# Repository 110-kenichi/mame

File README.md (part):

MAmidiMEmo 6.4.2.1 Itoken (c)2019, 2025 / GPL-2.0

*** What is the MAmidiMEmo? ***

MAmidiMEmo is a virtual chiptune sound MIDI module using a MAME sound engine.
You can control various chips and make sound via MIDI I/F.
So, you don't need to use dedicated tracker and so on anymore. You can use your favorite MIDI sequencer to make a chip sound.

See samples
https://www.youtube.com/channel/UCGYO2bEPPIM2LTNDbBEDaAQ

MAmidiMEmo adopts multi timbre method. That mean you can play multi chords on MIDI 1ch if the chip has multi ch.

e.g.) YM2151 has 8ch FM sounds, so you can play 8 chords on MIDI 1ch or sharing 8ch with MIDI 16ch like a SC-55 and so on.
      As well, NES APU has 2ch for square wave, so you can play 2 chords on MIDI 1ch when select a square wave timbre.
	  However, when you select a triangle wave timbre, you can play 1 chord on MIDI 1ch. Because NES APU has only 1ch for triangle wave.

*** How to use MAmidiMEmo ***

0. Requirements

	*H/W

		CPU: Intel Core series CPU or equivalent, at least 2.0 GHz
		MEM: at least 4GB
		Sound: DirectSound capable sound card/onboard audio
		MIDI: MIDI IN I/F

	*S/W

		OS: Windows 10 or lator
		Runtime: .NET Framework 4.7 or lator
		         VC++ 2022 Runtime
					for 64bit: https://aka.ms/vs/17/release/vc_redist.x64.exe
					for 32bit: https://aka.ms/vs/17/release/vc_redist.x86.exe

1. Extract downloaded zip file.

   And execute "Set-ExecutionPolicy -Scope Process -ExecutionPolicy Bypass" on the PowerShell to allow script execution.
   Then execute "DelZoneID.ps1" on the PowerShell to remove "Zone.Identifier" flag.
   
   ★日本語フォルダには現状対応していません★

2. Install VC++ runtime 2022 and .NET Framework 4.7 or lator.

3. Launch MAmidiMEmo.exe

   Note: You can change the value of audio latency, sampling rate and audio output interface by [Tool] menu.
         PortAudio is a low latency sound engine. See http://www.portaudio.com/
   Note: Allow ★firewall communication to MAmidiMEmo and your DAW.

4. Select MIDI I/F from toolbar. MAmidiMEmo will recevie MIDI message from the selected MIDI I/F.

   Note: You can use the loopMIDI (See http://www.tobias-erichsen.de/software/loopmidi.html) to send MIDI message from this PC to MAmidiMEmo.

5. Add your favorite chips from the [Instruments] menu on the toolbar.

   Note: Currently supported chips are the following.

        YM2151, YM2612, YM3812, YM2413, YM2610B, YMF262
		YM2601 ★★★ Place legitimate ym2608_adpcm_rom.bin file in the Mami dir ★★★
        SID, POKEY, GB APU, SN76496, NES APU, MSM5232(+TA7630), AY-3-8910
        NAMCO CUS30, SCC, HuC6280
        C140, SPC700
        MT-32 ★★★ Place legitimate MT32_CONTROL.ROM and MT32_PCM.ROM files in the Mami dir ★★★
		CM-32P This is an incomplete simulator, not an emulator.
		       You can mod and add your custom sounds by editing tbl and sound font files.
		       Please contact me if you can help me to create CM-32P and SN-U110 sound fonts.
		TMS5220, SP0256, SAM

   Note: You can add the chip up to 8 per same chip type and MAmidiMEmo eats more CPU power.

6. Select the chip from the left pane and configure the chip on the right pane.

   *[Timbres]
    You can edit sound character from this property. It's selected by "Program Change" MIDI message.
	Please refer the following articles or MAME sources to understand these timbre parameters.

	YM2151:
	 https://www16.atwiki.jp/mxdrv/pages/24.html

	YM2612:
	 https://www.plutiedev.com/ym2612-registers
	 http://www.smspower.org/maxim/Documents/YM2612

	NES APU:
	 http://hp.vector.co.jp/authors/VA042397/nes/apu.html
	 https://wiki.nesdev.com/w/index.php/APU
	 https://wiki.nesdev.com/w/index.php/APU_DMC

	GB APU:
	 http://bgb.bircd.org/pandocs.htm#soundcontrolregisters
	 https://gbdev.gg8.se/wiki/articles/Gameboy_sound_hardware
	 http://mydocuments.g2.xrea.com/
	 http://marc.rawer.de/Gameboy/Docs/GBCPUman.pdf
	 http://www.devrs.com/gb/files/hosted/GBSOUND.txt

	NAMCO CUS30:
     https://www.walkofmind.com/programming/pie/wsg3.htm
	 http://fpga.blog.shinobi.jp/fpga/おんげん！

	SN76489:
	 http://www.smspower.org/Development/SN76489
	 http://www.st.rim.or.jp/~nkomatsu/peripheral/SN76489.html

	SCC:
	 http://bifi.msxnet.org/msxnet/tech/scc.html

	YM3812:
	 http://www.oplx.com/opl2/docs/adlib_sb.txt

	YM2413:
	 http://d4.princess.ne.jp/msx/datas/OPLL/YM2413AP.html#31
	 http://www.smspower.org/maxim/Documents/YM2413ApplicationManual
	 http://hp.vector.co.jp/authors/VA054130/yamaha_curse.html

	MSM5232(+TA7630):
	 http://www.citylan.it/wiki/images/3/3e/5232.pdf
	 http://sr4.sakura.ne.jp/acsound/taito/taito5232.html

	AY-3-8910:
	 http://ngs.no.coocan.jp/doc/wiki.cgi/TechHan?page=1%BE%CF+PSG%A4%C8%B2%BB%C0%BC%BD%D0%CE%CF
	 https://w.atwiki.jp/msx-sdcc/pages/45.html
	 http://f.rdw.se/AY-3-8910-datasheet.pdf

	SID:
	 https://www.waitingforfriday.com/?p=661#6581_SID_Block_Diagram
	 http://www.bellesondes.fr/wiki/doku.php?id=mos6581#mos6581_sound_interface_device_sid
	 https://www.sfpgmr.net/blog/entry/mos-sid-6581を調べた.html

	HuC6280:
	 http://www.magicengine.com/mkit/doc_hard_psg.html

	SPC700:
	 https://wiki.superfamicom.org/spc700-reference

	POKEY:
	 https://en.wikipedia.org/wiki/POKEY
	 http://ftp.pigwa.net/stuff/collections/SIO2SD_DVD/PC/RMT%201.19/docs/rmt_en.htm
	 https://www.atariarchives.org/dere/chapt07.php
	 http://user.xmission.com/~trevin/atari/pokey_regs.html

	YM2610:
	 http://www.ajworld.net/neogeodev/ym2610am2.html

    MT-32:
     https://sourceforge.net/projects/munt/
     http://lib.roland.co.jp/support/jp/manuals/res/1809744/MT-32_j2.pdf

    CM-64:
	 http://lib.roland.co.jp/support/jp/manuals/res/1809003/CM-64_j.pdf

	YMF262:
	 http://map.grauw.nl/resources/sound/yamaha_ymf262.pdf

	YM2608:
     https://www.quarter-dev.info/archives/yamaha/YM2608_Applicatin_Manual.pdf

	TMS5220
	 https://www.dexsilicium.com/tms5220.pdf
     http://www.stuartconner.me.uk/ti_portable_speech_lab/ti_portable_speech_lab.htm

	SP0256
	 http://spatula-city.org/~im14u2c/sp0256-al2/Archer_SP0256-AL2.pdf

	SAM
	 https://github.com/s-macke/SAM
	 http://www.retrobits.net/atari/sam.shtml

	uPD1771
	 http://takeda-toshiya.my.coocan.jp/scv/scv.pdf

   *[Channels]
    Select which MIDI ch messages the chip receives.

7. Play MIDI file by your favorite sequencer or player.
   Of course, you can connect your favrite keyboard to MAmidiMEmo for live performance.

   MAmidiMEmo currently supports the following MIDI messages.

    Note On with velocity
    Note Off
    Program Change
	Control Change
		Pitch and PitchRange
		Volume and Expression
		Panpot
		Modulation, Modulation Depth, Modulation Range, Modulation Delay
		Portamento, Portamento Time
		All Note Off, (All Sound Off)
		CC#126/127 Mono/Poly mode. Spec is almost same with FITOM.
		Sound Control (for modifying a Timbre properties dynamically)
		Effect Depth (for modifying a VST properties dynamically)
		General Purpose Control (for modifying an instrument properties dynamically)

8. Also, you can set the following sound driver settings from Timbre settings.

   Arpeggio
   ADSR
   Effect (Pitch/Volue/Duty macro)

9. You can modify current timbre parameters via Sound control MIDI Message (70-75,79) dynamically.
   You can modify VST parameters via Effect Depth control MIDI Message (91-95) dynamically.
   You can modify other parameters via General Purpose control MIDI Message (16-19,80-83) dynamically.

10. You can modify receving MIDI ch for the specific instrument via NRPN MIDI Message.

   NRPN format is the following.

   Bx 63 41
   Bx 62 <Device ID> ... Specify Device ID of existing instrument.
   Bx 26 <Unit No>   ... Specify Unit No of the above Device ID of existing instrument.
   Bx 06 <Receiving MIDI ch(1-7) bit sets. 1=On, 0=Off>

         bit  6  5  4  3  2  1  0
	      ch   7  6  5  4  3  2  1

   Bx 63 42
   Bx 62 <Device ID> ... Specify Device ID of existing instrument.
   Bx 26 <Unit No>   ... Specify Unit No of the above Device ID of existing instrument.
   Bx 06 <Receiving MIDI ch(8-14) bit sets. 1=On, 0=Off>

         bit  6  5  4  3  2  1  0
	      ch  14 13 12 11 10  9  8

   Bx 63 43
   Bx 62 <Device ID> ... Specify Device ID of existing instrument.
   Bx 26 <Unit No>   ... Specify Unit No of the above Device ID of existing instrument.
   Bx 06 <Receiving MIDI ch(15-16) bit sets. 1=On, 0=Off>

         bit  6  5  4  3  2  1  0
          ch xx xx xx xx xx 16 15

11. (TBD)
   You can modify current environment and all timbre parameters via System Exclusive MIDI Message.

   Master Volume: "F0 7F 7F 04 01 00 nn F7"

	YM2151:(TBD)
	YM2612:(TBD)
	NES APU:(TBD)
	GB APU:(TBD)
	NAMCO CUS30:(TBD)
	SN76489:(TBD)
	:::

12. SPFM

   You can use a real sound chip instead of software emulation chip.
   Currently supported chips are YM2151 and YM2608 on SPFM.
   Before using the SPFM, you must setup SCCI by using the scciconfig.exe.

13. VSIF

	You can use a real machine instead of software emulation chip.
	Please see tha manual.
	https://github.com/110-kenichi/mame/blob/master/docs/MAmidiMEmo/Manual.pdf

*** ★Known issues and limitations★ *** 

   1. ★日本語フォルダには現状対応していません★
   2. You need to ★save the data ★manually on the DAW (Cubase and so on). Or, keep open the dummy editor window of the MAmidiMemo.
   3. Allow ★firewall communication to MAmidiMEmo and your DAW.
   4. MT-32 & CM32-P can not store/restore last settings.
   5. HuC6820 suddenly stop sounding. Please restart MAmi.
   6. MAmidiMEmo process stuck after sound interface changed if you used SCCI interface.
   
*** How to create build environment ***

   1. Install *LATEST* Visual Studio 2022 w/ VC++, C#, Windows Universal CRT SDK, .NET 4.7 SDK and Targeting Pack
   2. Install Windows 8.1 SDK and 10 SDK
   3. Install MinGW Development Environment(https://www.mamedev.org/tools/)
   4. Install vcpkg

*** Donate for supporting the MAmidiMEmo *** 

*** Changes
- 6.4.2.1 Fixed DMC Envelope property.
- 6.4.2.0 Added DMC Envelope property to the RP2A03 Fx.
- 6.4.1.0 Check if there is a difference in sample rate between the DAW and MAmi.
- 6.4.0.0 Added VST3 version VST plugin.
- 6.3.1.0 When selecting a file in Timbre Manager, you can test play the first sound in the list.
- 6.3.0.0 Added MIDI Controller Dialog. You can open the dialog from the Tool menu.
- 6.2.3.0 Added ModulationOverride, PanOverride, PitchOverride properties to MIDI Driver Settings of Timre property.
- 6.2.2.0 Supported "SPC700_for_MeSX" for MAmidiMemo
- 6.2.1.0 Supported MSXπ UART(i8251) for MAmidiMemo
  - Slightly may improved transfer speed MSXπ UART(i8251)
- 6.2.0.1 Fixed OPNB wait for MSXπ UART(i8251).
- 6.2.0.0 Supported MSXπ UART(i8251).
  - Use VGMPlay_mpi.rom (or VGMPlay_mpi_Vkey.rom)
  - Use MSXπ i8251 firmware(https://github.com/piigaa-densetu-two-dai/MSXpi_typeA/tree/main/i8251)
  - Supported NEOTRON(for VGMPlayer )
- - 6.1.7.0 Improved performance fo Piano pane rendering. 
  - Fixed SSG Envelope does not sound on YM2608.
- 6.1.6.1 Fixed an issue where sound would not stop on HuC6280. 
- 6.1.6.0 Updated VST Host libraries to the latest version. No need to install VC++ runtime 2012.
- 6.1.5.0 Improved property displaying performance for FM synthesis chips.
- 6.1.4.0 Improved algorithm of Praat2LPC for VLM5030.
- 6.1.3.0 Updated template file for praat for VLM5030.
- 6.1.2.0 Added Praat2LPC tool to the TMS5220 folder. You can create custom raw LPC data using this tool.
- 6.1.1.1 Fixed ToneType of the TMS5220 does not restore properly.
- 6.1.1.0 Added CustomLpcRawData property to the TMS5220. You can set custom raw LPC data.
  - Added custom raw LPC data creation tool to the MAmidiMEmo .\Tools\TMS5220 folder. You need to download Praat and VideoTools to use this tool.
- 6.1.0.0 Supported TIA(ATARI 2600).
- 6.0.5.4 Fixed MT-32 BIOS ROM loading path. No longer need to place MT32_CONTROL.ROM and MT32_PCM.ROM in the VST Host directory.
- 6.0.5.3 Re-improved Hi-DPI screen handling.
- 6.0.5.2 Fixed SysEx message handling for VSTi
- 6.0.5.1 Change default sample rate of PAULA_8364(AMIGA) to 16574Hz.
- 6.0.5.0 Change default sample rate of PAULA_8364(AMIGA) to 16574Hz.
  - Added RemoveMaxPeriodRistriction property to PAULA_8364(AMIGA).
- 6.0.4.3 Fixed PAULA_8364(AMIGA) loop calculation.
- 6.0.4.2 Fixed PAULA_8364(AMIGA) emulator sound engine.
- 6.0.4.1 Fixed the Timbre Manager  for PAULA_8364(AMIGA) while connecting to a real AMIGA.
  - Fixed event handler does not released on Forms
  - Fixed PAULA_8364(AMIGA) frequency calculation.
  - Fixed PAULA_8364(AMIGA) loop calculation.
  - Fixed PAULA_8364(AMIGA) PCM MAX size is 128K.
- 6.0.4.0 Supported the Timbre Manager for PAULA_8364(AMIGA).
- 6.0.3.0 Supported Loop Point PAULA_8364(AMIGA).
  - Limitation1: The length of the PCM must be at least 2 bytes.  
  - Limitation2: Does not support too short/too early loop point.  
- 6.0.2.3 Fixed PAULA_8364(AMIGA) Wait I/O error.
- 6.0.2.2 Fixed PAULA_8364(AMIGA) annoying noize issue.
- 6.0.2.1 Fixed PAULA_8364(AMIGA) freezing issue.
- 6.0.2.0 Improved UART transmission of PAULA_8364(AMIGA).
- 6.0.1.0 Supported importing *.sf file to PAULA_8364(AMIGA).
  - PAULA_8364(AMIGA) can export a default.vpcm file. VSIF_AMIGA driver can load the default.vpcm file on startup.
- 6.0.0.0 Supported PAULA_8364(AMIGA).
- 5.9.1.0 Supported 2nd PSG for MSX for VGMPlyer.
- 5.9.0.0 Supported NanoDrive 6 UART for OPN2, DCSG.
- 5.8.2.0 Added Push/Pop Tone button on the FM Timbre Editor.
- 5.8.1.6 Supported a VRC7 VGM file by VGMPlayer w/ MAmiCart + VRC7 cart.
- 5.8.1.5 Re-fixed FTDI clk handling for NES.
- 5.8.1.4 Fixed FTDI clk handling. This reduces the problem, especially if the clk value is changed for each chip on the MSX.
- 5.8.1.3 Temporary Fixed FTDI MSX FTDI clk value to stop SCC/OPLL properly. Please update MSX VSIF Driver ROM, too.
- 5.8.1.2 Fixed NES APU initial sounds register value of VGMPlayer.
- 5.8.1.1 Fixed FDS sounds stop routine of VGMPlayer.
- 5.8.1.0 Supported VSIF - PC Engine w/ Turbo EverDrive by MAmidiMEmo.
- 5.8.0.2 Fixed FDS hi frequency calculation.
- 5.8.0.1 Improved HuC6280 VGM file playing performance of VGMPlayer.
- 5.8.0.0 Supported HuC6280 VGM file playing on PC Engine(TG16) w/ Turbo EverDrive by VGMPlayer.
- 5.7.5.4 Fixed VGMPlayer(only) for YM2610 ADPCM file reading.
- 5.7.5.3 Supported YM2610 VGM file by OPN2 w/ DAC or tR DAC.
- 5.7.5.2 Supported YM2610 VGM file by OPNA w/ Pseudo DAC for non-turboR.
- 5.7.5.1 Fixed VGMPlayer(only) for YM2610 ADPCM.
- 5.7.5.0 Supported YM2610 VGM file by OPNA w/ turboR DAC on VGMPlayer(only). Please update MSX VSIF Driver ROM, too.
- 5.7.4.2 Fixed MSX VSIF Driver ROM for SCC-I.
- 5.7.4.1 Fixed VGMPlayer(only) to fix OPLL wait.
- 5.7.4.0 Fixed MSX VSIF Driver ROM for SCC.
  - Added vgmrips browser to download & play tracks on the VGMPlayer.
  - Updated 3rd party libraries. 
- 5.7.3.1 Updated VGMPlayer(only) to show Cover Art on the display(MSXturboR Only). Select Enable/Disable on the Settings dialog.
- 5.7.3.0 Added "Smart DAC Clipping" feature to MAmidiMEmo(OPN2, OPNA, NES).
  - Added DAC Clipping indicator to VGMPlayer.
- 5.7.2.4 Added "Smart DAC Clipping" feature to VGMPlayer.
  - Fixed Fixed PCM chip does not sounding properly on VGMPlayer. 
- 5.7.2.3 Fixed VGMPlayer(only) to fix MSM6258.
  - Fixed OPM Busy Wait to fix VSIF turboR(FTDI).
- 5.7.2.2 Fixed MEGA CD(VSIF Genesis(FTDI)) driver TYPO.
- 5.7.2.1 Updated VGMPlayer(only) to fix SCC sounding.
- 5.7.2.0 Improved MSX VSIF driver performance.
  - Included MEGE DRIVE driver on MEGA CD(VSIF Genesis(FTDI)) driver.
- 5.7.1.6 Improved MSX VSIF driver performance
  - Fix Sound off timing for VSIF OPLL
- 5.7.1.5 Updated VGMPlayer(only)
  - turboR DAC off when start/stop song.
  - turboR tR DAC off when start/stop song.
  - If you select turboR, the turboR DAC takes precedence over the OPN DAC; if you select MSX, the turboR DAC is not used.
- 5.7.1.4 Updated VGMPlayer(only) to fix MSXturboR DAC ADDA mode.
- 5.7.1.3 Updated VGMPlayer(only) to fix loop counter.
- 5.7.1.2 Updated VGMPlayer(only) to support MSXturboR DAC to play SEGA PCM, K053260, OKIM628- 5.
- 5.7.1.1 Re-improved Hi-DPI screen handling.
- 5.7.1.0 Improved Hi-DPI screen handling.
- 5.7.0.0 Supported \*.mop\* file importing on TimbreManager.
- 5.6.18.0 Fixed Multi-Media Keys handling.
- 5.6.17.0 Fixed Hold Off MIDI message handling.
- 5.6.16.0 Fixed ch9-18 address calculation for OPL3 for SCCI.
- 5.6.15.0 Showed the program number name on ProgramNumbers property.
  - Fixed ModulationRateShift prop is not working property.
- 5.6.14.0 Added external tool path settings on the Option dialog. Youcan launch the tool from the FM Tone Editor.
- 5.6.13.0 Added properties regarding modulation offset to the Midi Driver Settings on a Timbre.
- 5.6.12.1 Fixed some VGM file's tempo is too slow. (Rate values in VGM files are now ignored.)
- 5.6.12.0 Fixed AMD,PMD for OPM and OPZ. AMD and PMD can be handled simultaneously rather than exclusively.
  - OPM engine changed to the ymfm.
- 5.6.11.0 Supported VGI file importing.
  - Fixed some missing register values when importing FM tone files.
- 5.6.10.0 FM TimbreEditor allows copy/paste tone data from/to Clipboard.
  - Fixed Pcm data loading size is too long.
  - Improved DAC transfer rate.
- 5.6.9.1 Fixed MaxDacPcmVoices causes exception.
  - Included manuals
- 5.6.9.0 Improved FM Editor function.
- 5.6.8.2 Fixed XGM2 PCM.
- 5.6.8.1 Fixed XGM/XGM2 Recording.
  - Fixed an issue where pressing the Enter key would unintentionally close the editor window.
  - Fixed sequential numbering of saved file names
- 5.6.8.0 Fixed play status icon in LCD area does not change after playing stopped.
  - Remembered FM register patch file path information for FM Timbre.
  - Added "Privacy" settings to the settings dialog.
  - Enabled turboR mode for VSIF for MSX (VGM_msx*.rom). ( Pressing Z key to disable tR mode while booting ) 
- 5.6.7.0 Added MIDI ChanelTypes value "Drum(Ignore GateTime)".
- 5.6.6.1 Fixed DAC in YM2612 Software SoundEngine.
- 5.6.6.0 Supported DAC in YM2612 Software SoundEngine. (Other chips are available upon your request)
- 5.6.5.1 Fixed Timbre.AssignMIDIChtoSlotNumOffset not working properly.
- 5.6.5.0 Supported 24bit WAVE file importing.
  - Added Timbre List Window. You can open it from context menu of the Instrument icon.
  - Fixed FM Editor DR, SL lines drawing for OPL series.
- 5.6.4.0 Added MRU and autocomplete function to directory textbox in TimbreManager.
  - Fixed MonoMode may not work properly when CombinedTimbre is sounded.
- 5.6.3.0 Fixed problem with Timbre being replaced when dragging and dropping WAV files.
  - Added the function to set DrumTimbre as well in TimbreManager.
- 5.6.2.2 Changed the copy function of Timbre when drag & drop in TimbreManager and DrumEditor from the Shift key to the Ctrl key.
- 5.6.2.1 Supported YM2149 with YM2608/YM2203 for VGMPlayer
  - Swap Shift key effect for Drag & Drop in TimbreManager and DrumEditor.
- 5.6.2.0 Supported SAA1099 for VSIF MSX(FTDI) both MAmidiMEmo and VGMPlayer. You need to update VGM_msx*.rom too.
- 5.6.1.0 Added KeyOffStop property to FxS settings. To select envelope release timing of FxEngine when key off.
- 5.6.0.0 Supported SAA1099.
  - Fixed envelope release timing of FxEngine when key off.
  - (Preliminary) Supported XGM2 recording and fixed XGM PCM data.
- 5.5.0.2 Fixed supporting RF5C68.
- 5.5.0.0 Supported G.I.M.I.C STIC OPLL, OPN2*, SPSG, SSG, AYPSG.
  - Supported playing RF5C68 vgm data on MEGA-CD via VGMPlayer.
- 5.4.4.0 Supported WAV sample rate auto conversion.
- 5.4.3.2 Fixed crashing while launching the x86 MAmi.
  - (Experimentaly) Supported MSX turbo R mode for VSIF. Pressing "Z" key while booting the VGM_msx.rom/VGM_msx_Vkey.rom
- 5.4.3.1 Added SMS only special mode for FTDI dongle. OPLL and DSCG can sound simultenaously.
- 5.4.3.0 Supported mopm/mopn file importing to OPN*/OPM
  - ★Breaking changes★ Fixed the effect of modulation effects of the ModulationDepthes property.
- 5.4.2.0 Fixed incorrect soundding in mono mode.
- 5.4.1.0 Supported SPFM for YM2413, YM3812, YMF262, YM3806
- 5.4.0.1 Fixed SMS(FTDI) clk generator.
- 5.4.0.0 Supported SMS(FTDI). FTDI dongle is compatible with for the Genesis.
- 5.3.0.1 Fixed minor bugs related with Font. 
- 5.3.0.0 Added Font scale option in the Settings dialog. But not perfect.
- 5.2.2.0 Added KeyScaleLevel property on the FxS.
- 5.2.1.0 Suported MEGA CD(VSIF Genesis(FTDI)) vgm by VGMPlayer.
  - Note1: No supported streaming vgm data.
  - Note2: There is noise at the start of playback.
- 5.2.0.1 Fixed loop off processing for MEGA CD(VSIF Genesis(FTDI)).
- 5.2.0.0 Supported RF5C164 and MEGA CD(VSIF Genesis(FTDI)).
- 5.1.0.1 YM2608 Software Emulation can not be played via RPC.
- 5.1.0.0 Supported YM2608 for RPC server feature. Other applications can control MAmidiMEmo chips via RPC.
- 5.0.1.0 Added the ability to specify the number directly in the TimbreNumber setting.
- 5.0.0.9 Fixed LoopPoint value when importing SF2 file as 12bit PCM for SEGA MultiPCM.
- 5.0.0.8 Fixed noise sounding when D1R is too low for SEGA MultiPCM.
- 5.0.0.7 Supported 12bit PCM for SEGA MultiPCM
- 5.0.0.6 Fixed importing WAV file for SEGA MultiPCM. You NEED to re-create MultiPCM instrument.
- 5.0.0.5 Fixed Panpot for SEGA MultiPCM.
  - Reduced internal gain level for SEGA MultiPCM.
- 5.0.0.4 Fixed LoopPoint calculation for SEGA MultiPCM.
  - Fixed BaseFreq when import SF2.
- 5.0.0.3 (Again)Fixed frequency calculation for SEGA MultiPCM.
- 5.0.0.2 Supported MasterClock and 12bit RAW PCM for SEGA MultiPCM.
- 5.0.0.1 Fixed frequency and master clock for SEGA MultiPCM.
- 5.0.0.0 Supported SEGA MultiPCM.
- 4.9.10.1 Updated VGMPlayer(only) to support PC-8801 OPNA/OPN
- 4.9.10.0 Added DAC PCM mode for OPNA. Just a bonus feature :-)
- 4.9.9.0 Supported PC-8801 OPNA
- 4.9.8.1 Fixed an error on UseAltVRC6Cart prop value set by slider.
- 4.9.8.0 FtdiClkWidth to be adjusted when the VSIF connection is to FT232R or not.
- 4.9.7.1 Fixed SCC not sounding properly.
- 4.9.7.0 Added PcmData12 property to support 12bit PCM data for C140 chip. *Warning* For 12-bit PCM data, the Gain value should be lower than for 8-bit PCM data.
- 4.9.6.1 Fixed OPNA/B BaseFreq calculation algorithm when WAV file loading. ( 55000Hz -> 55555.55...Hz )
- 4.9.6.0 Fixed RP2A03 VRC6 and FDS upper pitch is 4bit from 3bit.
  - Fixed RP2A03 FDS velocity calculation and added FdsMasterVolume property.
  - Fixed RP2A03 LFO values are not set properly and caclulated.
  - Added RP2A03 Lfo Bias properly.
- 4.9.5.0 Fixed SP0256 freezing on high frequency sound.
  - Added the UseAltVRC7Cart property for YM2413 as experimental
  - Fixed unstable reconnection to the SPC700 on the G.I.M.I.C .
- 4.9.4.0 Preliminary supported VRC7 (VSIF - Famicom VRC6/7) as YM2413 variant chip DS1001.
- 4.9.3.1 Fixed SPC700 emulator keyon/keyoff
- 4.9.3.0 Supported a real chip of the SPC700 on the G.I.M.I.C .
- 4.9.2.0 Supported MAmi VRC6 CART for RP2A03.
- 4.9.1.2 Fixed YM2610B ADPCM-A keyon/keyoff is not working properly.
- 4.9.1.1 Fixed YM2610B ADPCM-B panpot is not working properly.
- 4.9.1.0 Updated dependent libraries.
  - Fixed SCC/LFO morphing envelopes of SDS.Fx. 1st envelope was not applied properly.
  - Fixed WSG editor. Text editing values were not reflected to GUI properly.
- 4.9.0.1 Fixed Receiving ch is not working properly.
- 4.9.0.0 Added MIDI THRU instrument.
  - Supported variable pitch and volume for RP2A03 DPCM.
- 4.8.2.1 Added VGM_P6M.bin for ROM Cartridge of PC-6001.
- 4.8.2.0 Added Copy button on the SCC WSG Morph Editor.
- 4.8.1.0 Improved VSIF stability and supported DAC PCM(Real only) for Famicom ★Please update VGMPlay_nes*.nes
- 4.8.0.0 Added SCC WSG Morph Editor.
  - Displayed the ToolTip in the FM Timbe Editor only once.
- 4.7.9.0 Improved VSTi close processing to avoid crashing on some DAWs.
  - Improved initialize routine for the Real Chip
  - Fixed VGM recording folder is not created.
- 4.7.8.2 Remove dummy VSTi window to avoid crashing.
- 4.7.8.1 Fixed GUI layout of the Dialog.
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
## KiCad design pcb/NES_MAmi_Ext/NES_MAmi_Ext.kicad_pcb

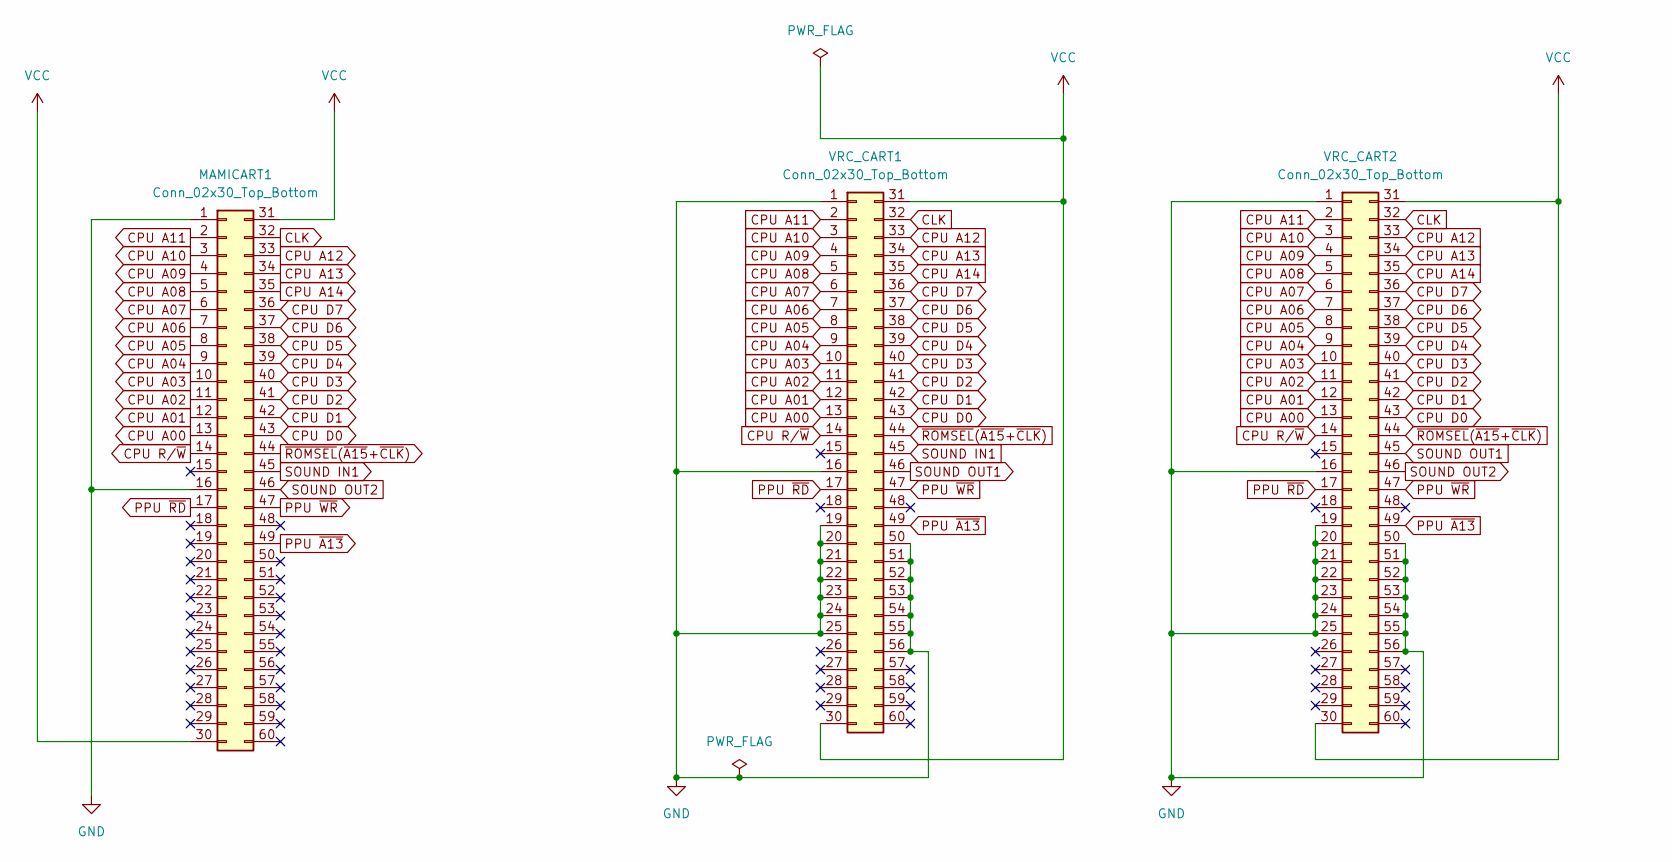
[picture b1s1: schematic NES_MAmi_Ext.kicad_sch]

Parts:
MAMICART1: Conn_02x30_Top_Bottom; FC_cardedge_60p
VRC_CART1, VRC_CART2: Conn_02x30_Top_Bottom; NES-CART-CONN

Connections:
CLK: MAMICART1.32, VRC_CART1.32, VRC_CART2.32
CPU A00: MAMICART1.13, VRC_CART1.13, VRC_CART2.13
CPU A01: MAMICART1.12, VRC_CART1.12, VRC_CART2.12
CPU A02: MAMICART1.11, VRC_CART1.11, VRC_CART2.11
CPU A03: MAMICART1.10, VRC_CART1.10, VRC_CART2.10
CPU A04: MAMICART1.9, VRC_CART1.9, VRC_CART2.9
CPU A05: MAMICART1.8, VRC_CART1.8, VRC_CART2.8
CPU A06: MAMICART1.7, VRC_CART1.7, VRC_CART2.7
CPU A07: MAMICART1.6, VRC_CART1.6, VRC_CART2.6
CPU A08: MAMICART1.5, VRC_CART1.5, VRC_CART2.5
CPU A09: MAMICART1.4, VRC_CART1.4, VRC_CART2.4
CPU A10: MAMICART1.3, VRC_CART1.3, VRC_CART2.3
CPU A11: MAMICART1.2, VRC_CART1.2, VRC_CART2.2
CPU A12: MAMICART1.33, VRC_CART1.33, VRC_CART2.33
CPU A13: MAMICART1.34, VRC_CART1.34, VRC_CART2.34
CPU A14: MAMICART1.35, VRC_CART1.35, VRC_CART2.35
CPU D0: MAMICART1.43, VRC_CART1.43, VRC_CART2.43
CPU D1: MAMICART1.42, VRC_CART1.42, VRC_CART2.42
CPU D2: MAMICART1.41, VRC_CART1.41, VRC_CART2.41
CPU D3: MAMICART1.40, VRC_CART1.40, VRC_CART2.40
CPU D4: MAMICART1.39, VRC_CART1.39, VRC_CART2.39
CPU D5: MAMICART1.38, VRC_CART1.38, VRC_CART2.38
CPU D6: MAMICART1.37, VRC_CART1.37, VRC_CART2.37
CPU D7: MAMICART1.36, VRC_CART1.36, VRC_CART2.36
CPU R/~W: MAMICART1.14, VRC_CART1.14, VRC_CART2.14
GND: MAMICART1.1, MAMICART1.16, VRC_CART1.1, VRC_CART1.16, VRC_CART1.19, VRC_CART1.20, VRC_CART1.21, VRC_CART1.22, VRC_CART1.23, VRC_CART1.24, VRC_CART1.25, VRC_CART1.50, VRC_CART1.51, VRC_CART1.52, VRC_CART1.53, VRC_CART1.54, VRC_CART1.55, VRC_CART1.56, VRC_CART2.1, VRC_CART2.16, VRC_CART2.19, VRC_CART2.20, VRC_CART2.21, VRC_CART2.22, VRC_CART2.23, VRC_CART2.24, VRC_CART2.25, VRC_CART2.50, VRC_CART2.51, VRC_CART2.52, VRC_CART2.53, VRC_CART2.54, VRC_CART2.55, VRC_CART2.56
PPU ~A13: MAMICART1.49, VRC_CART1.49, VRC_CART2.49
PPU ~RD: MAMICART1.17, VRC_CART1.17, VRC_CART2.17
PPU ~WR: MAMICART1.47, VRC_CART1.47, VRC_CART2.47
SOUND IN1: MAMICART1.45, VRC_CART1.45
SOUND OUT1: VRC_CART1.46, VRC_CART2.45
SOUND OUT2: MAMICART1.46, VRC_CART2.46
VCC: MAMICART1.30, MAMICART1.31, VRC_CART1.30, VRC_CART1.31, VRC_CART2.30, VRC_CART2.31
~ROMSEL(~A15+~CLK): MAMICART1.44, VRC_CART1.44, VRC_CART2.44

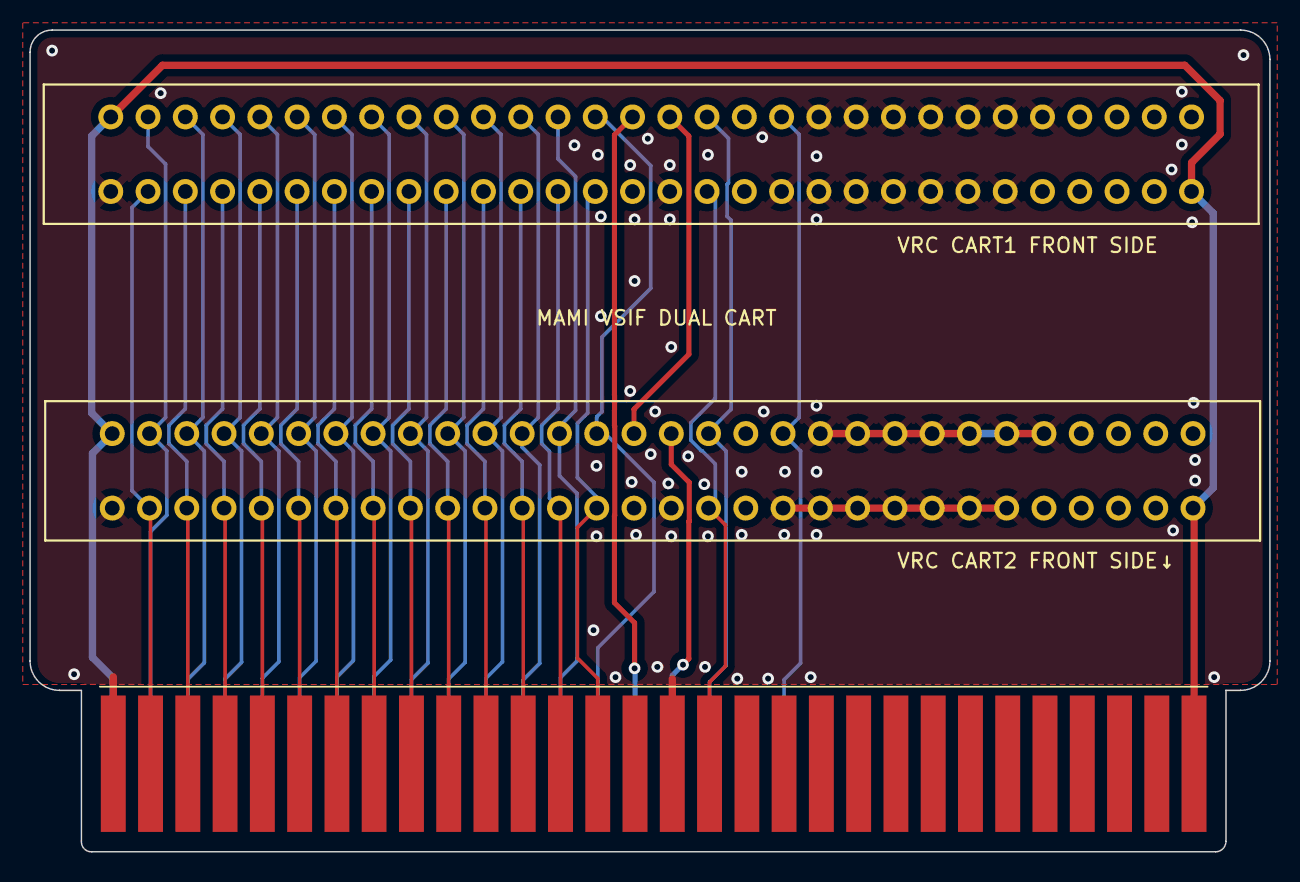
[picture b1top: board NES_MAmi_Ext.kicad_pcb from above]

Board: 2 copper layers, 84.5 x 56.0 mm, 3 parts (0 on the bottom side), 34 nets.

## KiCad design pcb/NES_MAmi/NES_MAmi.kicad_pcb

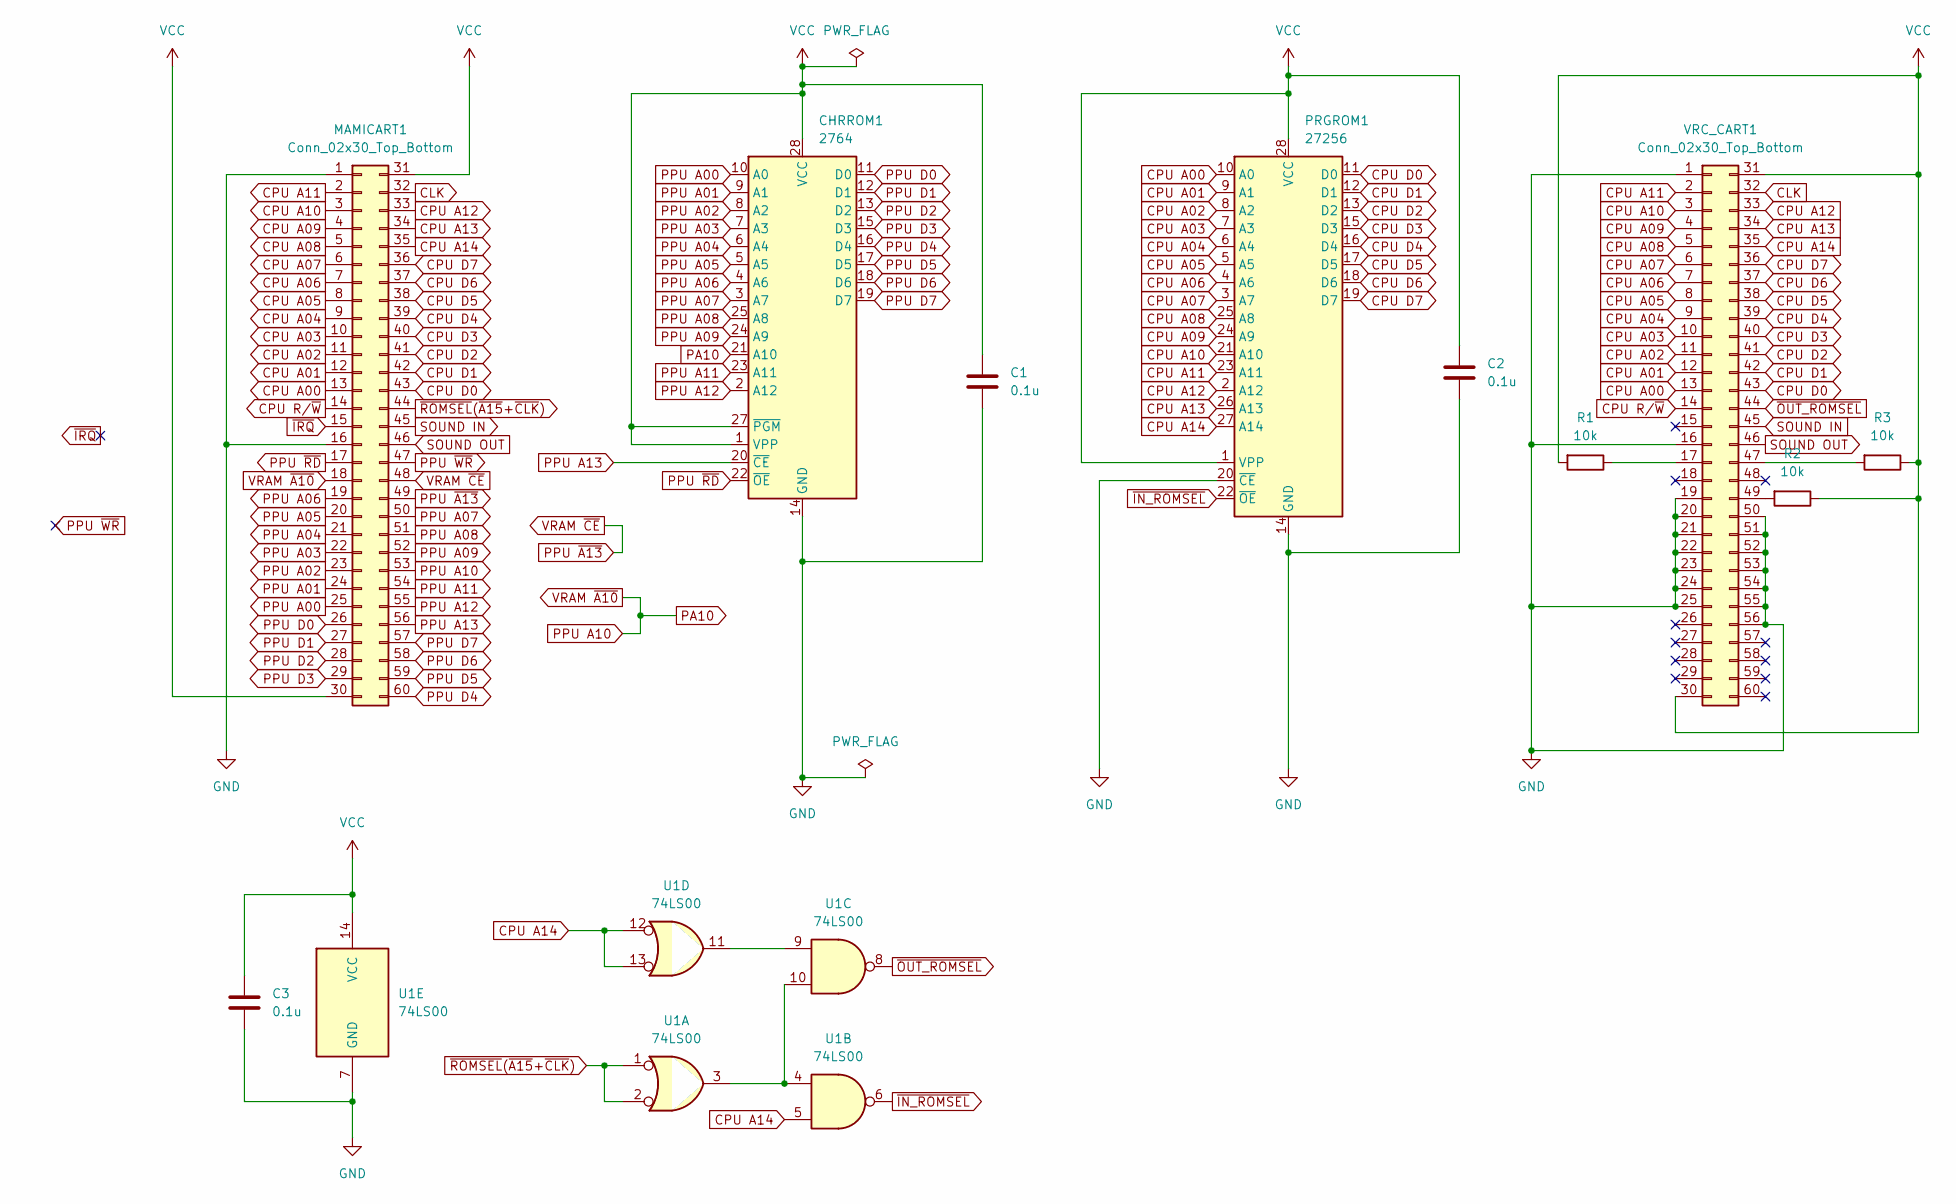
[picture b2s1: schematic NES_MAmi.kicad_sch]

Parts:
C1, C2, C3: 0.1u; C_Disc_D6.0mm_W2.5mm_P5.00mm
CHRROM1: 2764; DIP-28_W15.24mm
MAMICART1: Conn_02x30_Top_Bottom; FC_cardedge_60p
PRGROM1: 27256; DIP-28_W15.24mm
R1, R2, R3: 10k; R_Axial_DIN0207_L6.3mm_D2.5mm_P7.62mm_Horizontal
U1: 74LS00; DIP794W45P254L1969H508Q14
VRC_CART1: Conn_02x30_Top_Bottom; NES-CART-CONN

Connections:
CLK: MAMICART1.32, VRC_CART1.32
CPU A00: MAMICART1.13, PRGROM1.10 (A0), VRC_CART1.13
CPU A01: MAMICART1.12, PRGROM1.9 (A1), VRC_CART1.12
CPU A02: MAMICART1.11, PRGROM1.8 (A2), VRC_CART1.11
CPU A03: MAMICART1.10, PRGROM1.7 (A3), VRC_CART1.10
CPU A04: MAMICART1.9, PRGROM1.6 (A4), VRC_CART1.9
CPU A05: MAMICART1.8, PRGROM1.5 (A5), VRC_CART1.8
CPU A06: MAMICART1.7, PRGROM1.4 (A6), VRC_CART1.7
CPU A07: MAMICART1.6, PRGROM1.3 (A7), VRC_CART1.6
CPU A08: MAMICART1.5, PRGROM1.25 (A8), VRC_CART1.5
CPU A09: MAMICART1.4, PRGROM1.24 (A9), VRC_CART1.4
CPU A10: MAMICART1.3, PRGROM1.21 (A10), VRC_CART1.3
CPU A11: MAMICART1.2, PRGROM1.23 (A11), VRC_CART1.2
CPU A12: MAMICART1.33, PRGROM1.2 (A12), VRC_CART1.33
CPU A13: MAMICART1.34, PRGROM1.26 (A13), VRC_CART1.34
CPU A14: MAMICART1.35, PRGROM1.27 (A14), U1.5, U1.12, U1.13, VRC_CART1.35
CPU D0: MAMICART1.43, PRGROM1.11 (D0), VRC_CART1.43
CPU D1: MAMICART1.42, PRGROM1.12 (D1), VRC_CART1.42
CPU D2: MAMICART1.41, PRGROM1.13 (D2), VRC_CART1.41
CPU D3: MAMICART1.40, PRGROM1.15 (D3), VRC_CART1.40
CPU D4: MAMICART1.39, PRGROM1.16 (D4), VRC_CART1.39
CPU D5: MAMICART1.38, PRGROM1.17 (D5), VRC_CART1.38
CPU D6: MAMICART1.37, PRGROM1.18 (D6), VRC_CART1.37
CPU D7: MAMICART1.36, PRGROM1.19 (D7), VRC_CART1.36
CPU R/~W: MAMICART1.14, VRC_CART1.14
GND: C1.2, C2.2, C3.2, CHRROM1.14 (GND), MAMICART1.1, MAMICART1.16, PRGROM1.14 (GND), PRGROM1.20 (~CE), U1.7 (GND), VRC_CART1.1, VRC_CART1.16, VRC_CART1.19, VRC_CART1.20, VRC_CART1.21, VRC_CART1.22, VRC_CART1.23, VRC_CART1.24, VRC_CART1.25, VRC_CART1.50, VRC_CART1.51, VRC_CART1.52, VRC_CART1.53, VRC_CART1.54, VRC_CART1.55, VRC_CART1.56
unnamed: U1.3, U1.4, U1.10
unnamed: U1.9, U1.11
unnamed: R1.1, VRC_CART1.17
unnamed: R3.2, VRC_CART1.47
unnamed: R2.2, VRC_CART1.49
PA10: CHRROM1.21 (A10), MAMICART1.18, MAMICART1.53
PPU A00: CHRROM1.10 (A0), MAMICART1.25
PPU A01: CHRROM1.9 (A1), MAMICART1.24
PPU A02: CHRROM1.8 (A2), MAMICART1.23
PPU A03: CHRROM1.7 (A3), MAMICART1.22
PPU A04: CHRROM1.6 (A4), MAMICART1.21
PPU A05: CHRROM1.5 (A5), MAMICART1.20
PPU A06: CHRROM1.4 (A6), MAMICART1.19
PPU A07: CHRROM1.3 (A7), MAMICART1.50
PPU A08: CHRROM1.25 (A8), MAMICART1.51
PPU A09: CHRROM1.24 (A9), MAMICART1.52
PPU A11: CHRROM1.23 (A11), MAMICART1.54
PPU A12: CHRROM1.2 (A12), MAMICART1.55
PPU A13: CHRROM1.20 (~CE), MAMICART1.56
PPU D0: CHRROM1.11 (D0), MAMICART1.26
PPU D1: CHRROM1.12 (D1), MAMICART1.27
PPU D2: CHRROM1.13 (D2), MAMICART1.28
PPU D3: CHRROM1.15 (D3), MAMICART1.29
PPU D4: CHRROM1.16 (D4), MAMICART1.60
PPU D5: CHRROM1.17 (D5), MAMICART1.59
PPU D6: CHRROM1.18 (D6), MAMICART1.58
PPU D7: CHRROM1.19 (D7), MAMICART1.57
PPU ~A13: MAMICART1.48, MAMICART1.49
PPU ~RD: CHRROM1.22 (~OE), MAMICART1.17
PPU ~WR: MAMICART1.47
SOUND IN: MAMICART1.45, VRC_CART1.45
SOUND OUT: MAMICART1.46, VRC_CART1.46
VCC: C1.1, C2.1, C3.1, CHRROM1.1 (VPP), CHRROM1.27 (~PGM), CHRROM1.28 (VCC), MAMICART1.30, MAMICART1.31, PRGROM1.1 (VPP), PRGROM1.28 (VCC), R1.2, R2.1, R3.1, U1.14 (VCC), VRC_CART1.30, VRC_CART1.31
~IN_ROMSEL: PRGROM1.22 (~OE), U1.6
~IRQ: MAMICART1.15
~OUT_ROMSEL: U1.8, VRC_CART1.44
~ROMSEL(~A15+~CLK): MAMICART1.44, U1.1, U1.2

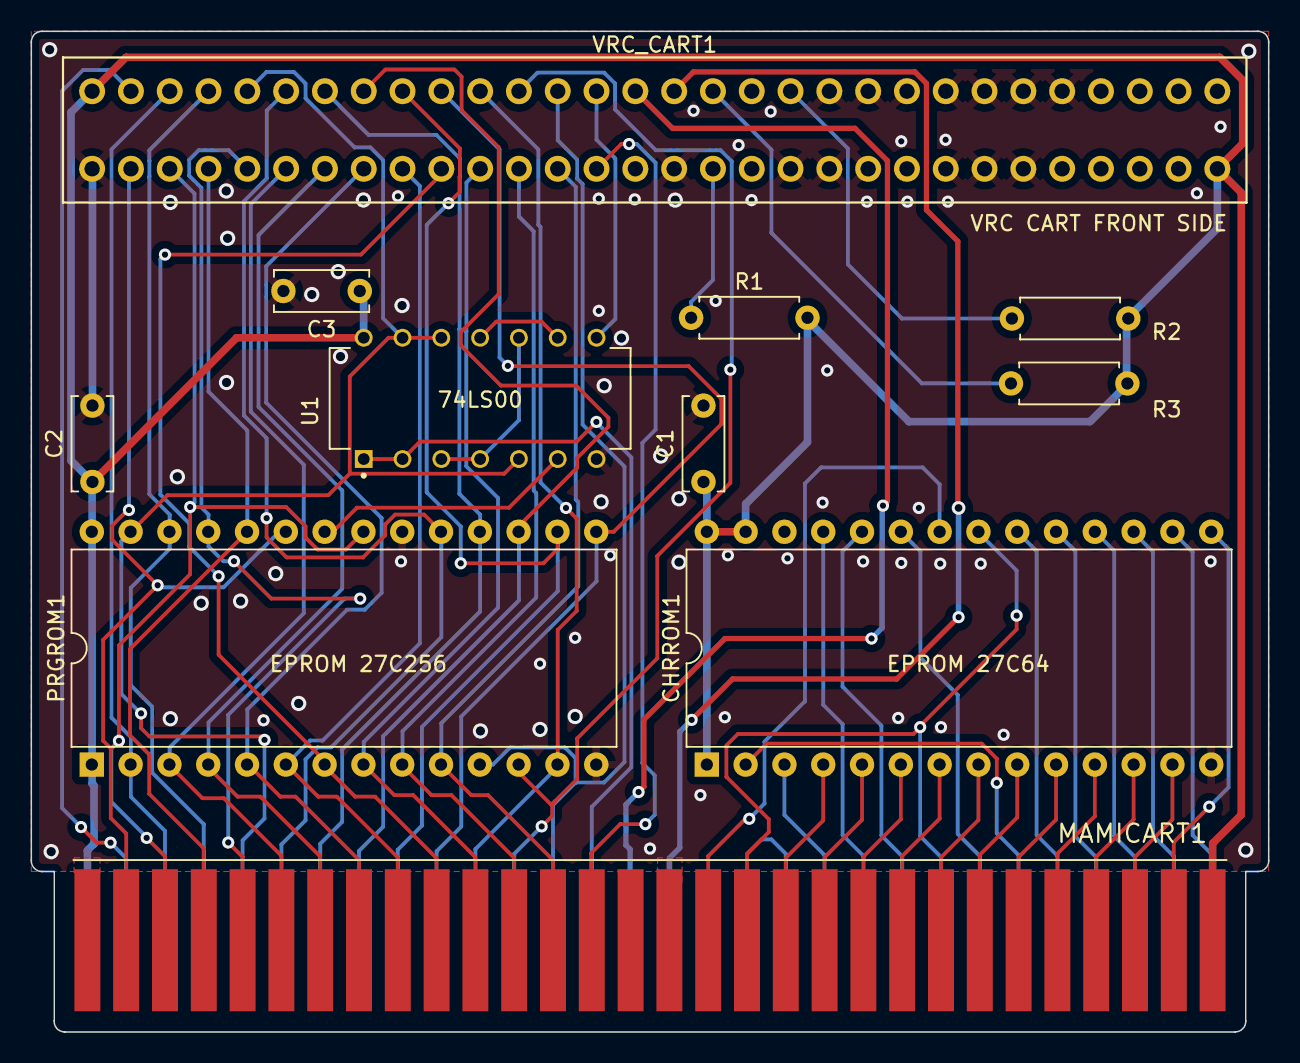
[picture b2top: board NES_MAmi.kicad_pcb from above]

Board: 2 copper layers, 81.0 x 65.5 mm, 11 parts (0 on the bottom side), 61 nets.

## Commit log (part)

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2022-12-11 Fixed first connecting sequence for VSIF FTDI
2022-12-11 Fixed ADPCM wait routine
2022-12-12 VGMPlayer_adpcm_burst
2022-12-13 - Fixed VGM header reader for a old vgm file
2022-12-15 - Initialized FM registers at playback starting.
2022-12-17 - Fixed VGM/XGM playback routine for VGMPlayer. - Added VGMPlay_msx_Vkey.rom (See the manual for details)
2022-12-19 4.5.5.3 Added chip clock converter for VGMPlayer.
2022-12-20 4.5.5.4 Fixed an exception occuring on Serialize property for CM32P & MT32.
2022-12-27 - Supported PC-6001 for VSIF(FTDI). VSIF(FTDI) spec is same as MSX.
2023-01-08 BitBangTest Tool
2023-01-15 4.5.7.1 Fixed a minor bug of VGMPlayer
2023-01-18 4.5.7.2.1 Fixed VGMPlayer for YM2612 DAC.
2023-01-23 4.5.8.0 - Renamed CM-32P user soundfont table sample file name. You need to remove "_memo" from tbl file name to use properly. - Changed MSX rom filename for for VSIF(FTDI) to VGM_msx*.rom from VGMPl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
2023-01-23 Supported the m3u playlist file for VGMPlayer.
2023-01-28 - Fixed typo "F#9" for CombinedTimbre KeyRange. (Thanks D.M.88-san!) - Fixed no-sounding when playing a VGM file contains dual chip mode.
2023-02-05 - Supported OPNA Pseudo DAC mode for OPN2 DAC mode
2023-02-09 - Supported PAN for pseudo DAC of OPNA for OPN2 - Adjust DAC volume for pseudo DAC of OPNA for OPN2
2023-02-14 Updated manual
2023-02-19 4.5.11.0 Improved VSIF(FTDI) transfer speed. Please reset & re-adjust FTDI clk width.
2023-02-26 updated manual (FM register editor)
2023-03-02 4.6.1.0 Re-fixed envelopes & MONO mode processing.
2023-03-05 - cleanup VSIF for MD
2023-03-12 4.6.3.0 Added the \"$\" keyword for the NoteMap property. The \"$\" keyword indicates its own value.
2023-03-18 - Fixed MGS file playing not started for VGMPlayer - Changed VelocityMap and NoteMap property behavior. Parameter changes are temporary, not permanent.
2023-03-20 4.6.5.0 Supported GIMIC for YM2608 & YM2151.
2023-03-20 - Supported GIMIC by VGMPlayer for OPM & OPNA - User DirectAccess API for GIMIC to avoid cache miss
2023-03-21 - Fixed OPM could not be selected on VGMPlayer
2023-03-22 - Supported OPN3-L for proxy of OPNA - Reset G.I.M.I.C before start playing a VGM or reset instrument. - Fixed freezing while ADPCM data transferring on YM2608 and RP2A03.
2023-03-24 4.6.5.7 Improved performance of G.I.M.I.C .
2023-03-25 - Added DAC volume adjust for proxy
2023-03-25 4.6.6.1 Tentatively fixed SID emulator output frequency changes when sample rate is other than 48KHz.
2023-03-26 4.6.7.0 Supported importing *.FF/*.FFOPM file.
2023-03-26 4.6.7.1 Fixed importing *.FF/*.FFOPM file. Fixed velocity is invalid.
2023-03-27 - Improved latency of VSTi module for certain DAW. - Added FineTunes Property. FineTunes Property can change RPN.
2023-03-29 Reduced crashing while closing DAW. (Preliminary) Added sin/sq/tri wave create button on the SW Envelope editor. (Preliminary) Supported LegatoFootSwitch(CC#68). Affected only MONO mode =1 and Recent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
2023-03-29 (Preliminary) Supported DAC PCM for YM2612 for REAL HARDWARE.
2023-03-30 Fixed XGM DAC wait
2023-03-30 - Increased DAC PCM 1ch to 4ch for YM2612
2023-04-01 output xgm
2023-04-02 Supported Import/Export FM tone file of MAmi format.
2023-04-02 4.6.10.0 Added SerializeData Save/Load feature Supported Import/Export FM tone file as MAmi format. Re-fixed Save/Load error on DAW. Fixed VGMPlay DAC volume.
2023-04-03 - Added DAC transfer disabling prop for OPN2
2023-04-04 - Supported XGM loop point specifying by NRPN
2023-04-05 Improved XGM
2023-04-06 - Improved data transfer speed for FTDI
2023-04-07 Fixed Copy/Paste menu enabled status
2023-04-07 Added ProcessingInterval property for Instrument. You can change LFO and Portament processing interval[ms] for a real machine to prevent performance hit.
2023-04-09 - Improved performance of DAC
2023-04-10 - Added Timbre Manager
2023-04-12 Fixed file type name on Timbre Manager
2023-04-12 - Fixed pseudo DAC for XGM
2023-04-13 Fixed CombinedTimbre name display
2023-04-13 Added DAC PCM Gain prop and Velocity Disable prop
2023-04-14 Improved TimbresManager functions
2023-04-15 MAmidiMEmo 4.7.2.0
2023-04-16 - Show Data Entry Value on a piano control as the Tooltip
2023-04-23 4.7.4.1 Supported K053260 for VGMPlayer.
2023-04-25 4.7.6.0 Improved DAC PCM souding timing & XGM/VGM player souding timing.
2023-04-28 - Supported OKIM6259 - Improved DAC stream performance for VGM file
2023-05-01 - Fixed freezing while YM2608 ADPCM transferring. - Fixed MasterClock handling for SPFM - Fixed CombinedTimbre delay sounding
2023-05-09 4.7.8.1 Fixed GUI layout of the Dialog.
2023-05-12 4.7.8.2 Remove dummy VSTi window to avoid crashing.
2023-05-13 added operation manual
2023-05-20 - Fixed VGM recording folder is not created
2023-05-29 - Changed VGIF for NES protocol
2023-05-30 - Improved VGIF for NES protocol
2023-05-30 4.8.2.0 Added Copy button on the SCC WSG Morph Editor.
2023-06-04 4.8.2.1 Added VGM_P6M.bin for ROM Cartridge of PC-6001.
2023-06-06 - Added description for optimal FtdiClkWidth
2023-06-07 - Supported DAC PCM(Real only) volume and loop for Famicom
2023-06-16 - Updated gerber data, circuit diagram, parts list, and product images of MAmi-VSIF dongle for MSX
2023-07-30 - Updated dependent libraries - Fixed SCC/LFO morphing envelopes of SDS.Fx. 1st envelope was not applied properly. - Fixed WSG editor. Text editing values were not reflected to GUI properly.
2023-08-01 4.9.1.2 Fixed ADPCM-A keyoff is not working properly.
2023-08-03 - Hide unused properties.
2023-08-06 4.9.3.1 Fixed SPC700 emulator keyon/keyoff
2023-08-13 - Fixed SP0256 freezing on high frequency sound - Added the UseAltVRC7Cart property for YM2413 as experimental
2023-08-14 4.9.6.0 Fixed RP2A03 VRC6 and FDS upper pitch is 4bit from 3bit. Fixed RP2A03 FDS velocity calculation and added FdsMasterVolume property. Fixed RP2A03 LFO values are not set properly and caclulated.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
2023-08-21 4.9.6.1 Fixed OPNA/B BaseFreq calculation algorithm when WAV file loading. ( 55000Hz -> 55555.55...Hz )
2023-08-22 4.9.7.1 Fixed SCC not sounding properly.
2023-09-22 4.9.9.0 Supported PC-8801 OPNA
2023-09-23 4.9.10.1 Updated VGMPlayer(only) to support PC-8801 OPNA/OPN
2023-10-08 5.0.0.1 Fixed frequency and master clock for SEGA MultiPCM.
2023-10-11 5.0.0.4 - Fixed LoopPoint calculation for SEGA MultiPCM. - Fixed BaseFreq when import SF2.
2023-10-12 5.0.0.6 Fixed importing WAV file for SEGA MultiPCM. You NEED to re-create MultiPCM instrument.
2023-10-14 - Fixed noise sounding when D1R is too low for SEGA MultiPCM.
2023-10-15 5.0.1.0 Added the ability to specify the number directly in the TimbreNumber setting.
2023-11-02 - Supported RF5C164
2023-11-03 5.2.1.0 Suported MEGA CD(VSIF Genesis(FTDI)) vgm by VGMPlayer. Note1: No supported streaming vgm data. Note2: There is noise at the start of playback.
2023-11-23 Added OpManual_VSIF_MD_ja.pdf
2023-12-07 5.3.0.0 Added Font scale option in the Settings dialog. But not perfect.
2023-12-24 5.4.0.1 Fixed SMS(FTDI) clk generator.
2023-12-27 5.4.2.0 Fixed incorrect soundding in mono mode.
2024-01-04 5.4.0.0 Supported SMS(FTDI)(SMS) mode for Master System. DCSG and FM can sound at same time.
2024-01-15 5.4.4.0 Supported WAV sample rate auto conversion.
2024-01-31 5.5.0.0 Supported G.I.M.I.C STIC OPLL, OPN2*, SPSG, SSG, AYPSG.
2024-02-02 5.5.0.1 Fixed supporting RF5C68.
2024-02-10 5.6.0.0 Supported SAA1099. Fixed envelope release timing of FxEngine when key off. (Preliminary) Supported XGM2 recording and fixed XGM PCM data.
2024-03-04 Supported YM2149 with YM2608/YM2203
2024-03-12 Added wait type selection Optimize DAC data stream
2024-03-19 5.6.2.2 Changed the copy function of Timbre when drag & drop in TimbreManager and DrumEditor from the Shift key to the Ctrl key.
2024-03-20 5.6.3.0 Added the function to set DrumTimbre as well in TimbreManager.
2024-03-23 5.6.5.0 Supported 24bit WAVE file importing. Added Timbre List Window. You can open it from context menu of the Instrument icon. Fixed FM Editor DR, SL lines drawing for OPL series.
2024-03-26 5.6.6.0 Supported DAC in YM2612 Software SoundEngine. (Other chips are available upon your request)
2024-03-27 5.6.7.0 Added MIDI ChanelTypes value "Drum(Ignore GateTime)".
2024-03-28 - Added sequential numbering to reduce the possibility of overwriting existing files when saving files.
2024-03-31 - Integratec FM Editor with Timbre Property editor.
2024-04-02 5.6.8.2 Fixed XGM2 PCM.
2024-04-05 - Added explanation of GateTime on Drum ch
2024-04-29 5.6.9.2 Add additional information for AssignMIDIChtoSlotNumOffset prop.
2024-05-19 5.6.11.0 Supported VGI file importing. Fixed some missing register values when importing FM tone files.
2024-06-01 5.6.12.1 Fixed some VGM file's tempo is too slow. (Rate values in VGM files are now ignored.)
2024-06-15 5.6.13.0 Added properties regarding modulation offset to the Midi Driver Settings on a Timbre.
2024-08-24 Fixed ModulationRateShift prop is not working property
2024-08-31 5.6.17.0 Fixed Hold Off MIDI message handling.
2024-10-16 5.7.1.0 Improved Hi-DPI screen handling.
2024-11-02 5.7.1.2 Updated VGMPlayer(only) to support MSXturboR DAC to play SEGA PCM, K053260, OKIM6285.
2024-11-04 - 5.7.1.5 Updated VGMPlayer(only) - turboR DAC off when start/stop song. - turboR tR DAC off when start/stop song. - If you select turboR, the turboR DAC takes precedence over the OPN DAC; if you sel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
2024-11-05 - 5.7.1.6 Improved MSX VSIF driver performance - Fix Sound off timing for VSIF OPLL
2024-11-07 - 5.7.2.1 Updated VGMPlayer(only) to fix SCC sounding.
2024-11-07 - 5.7.2.3 Fixed VGMPlayer(only) to fix MSM6258.
2024-11-09 - 5.7.2.4 Added "Smart DAC Clipping" feature to VGMPlayer. - Fixed Fixed PCM chip does not sounding properly on VGMPlayer.
2024-11-13 - 5.7.3.1 Updated VGMPlayer(only) to show Cover Art on the display(MSXturboR Only). Select Enable/Disable on the Settings dialog.
2024-11-16 - 5.7.4.0 Fixed MSX VSIF Driver ROM for SCC. - Added vgmrips browser to download & play tracks on the VGMPlayer. - Updated 3rd party libraries.
2024-11-17 - 5.7.5.0 Supported YM2610 VGM file by OPNA w/ turboR DAC on VGMPlayer(only). Please update MSX VSIF Driver ROM, too.
2024-11-18 - 5.7.5.2 Supported YM2610 VGM file by OPNA w/ Pseudo DAC for non-turboR.
2024-11-23 - 5.7.5.4 Fixed VGMPlayer(only) for YM2610 ADPCM file reading.
2024-12-11 - 5.8.0.1 Improved HuC6280 VGM file playing performance of VGMPlayer.
2025-01-07 - 5.8.1.1 Fixed FDS sounds stop routine of VGMPlayer.
2025-01-11 - 5.8.1.3 Temporary Fixed FTDI MSX FTDI clk value to stop SCC/OPLL properly. Please update MSX VSIF Driver ROM, too.
2025-01-19 - 5.8.1.5 Re-fixed FTDI clk handling for NES.
2025-02-10 - 5.8.2.0 Added Push/Pop Tone button on the FM Timbre Editor.
2025-04-01 VSIF AMIGA
2025-04-06 - 6.0.0.0 Supported PAULA_8364(AMIGA).
2025-04-09 Refactoring AMIGA
2025-04-10 - 6.0.2.1 Fixed PAULA_8364(AMIGA) freezing issue.
2025-04-13 - 6.0.2.3 Fixed PAULA_8364(AMIGA) Wait I/O error.
2025-04-19 - 6.0.4.0 Supported the Timbre Manager for PAULA_8364(AMIGA).
2025-04-23 - 6.0.4.2 Fixed PAULA_8364(AMIGA) emulator sound engine.
2025-04-24 - 6.0.5.1 Change default sample rate of PAULA_8364(AMIGA) to 16574Hz.
2025-05-04 - 6.0.5.3 Re-improved Hi-DPI screen handling.
2025-05-13 - 6.1.0.0 Supported TIA(ATARI 2600).
2025-05-16 - 6.1.1.1 Fixed ToneType of the TMS5220 does not restore properly.
2025-05-22 - 6.1.3.0 Updated template file for praat for VLM5030.
2025-06-03 - 6.1.5.0 Improved property displaying speed for FM synthesis chips.
2025-06-06 - 6.1.6.1 Fixed an issue where sound would not stop on HuC6280.
2025-07-13 (Pre)Supported MSX pi
2025-07-25 Supported MSX pi
2025-07-29 Added YM2610B MSX pi supporting
2025-09-04 - 6.2.2.0 Supported "SPC700_for_MeSX" for MAmidiMemo
2025-11-09 - 6.4.0.0 Added VST3 version VST plugin.

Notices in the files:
README.md:
DryWetMidi - Copyright (c) 2018 Maxim Dobroselsky
Newtonsoft.Json - Copyright © James Newton-King 2008
ValueInjecter - Copyright (c) 2015 Valentin Plamadeala
Fast Colored TextBox for Syntax Highlighting - Copyright (C) Pavel Torgashov, 2011-2016.
FluidLite -  (c) 2016 Robin Lobel
FM-SoundConvertor - Copyright (c) 2020 D.M.88
LegacyWrapper - Copyright (c) 2019 Franz Wimmer
FastDelegate.Net - Copyright (c) 2015 coder0xff
rpclib - Copyright (c) 2015-2017, Tamás Szelei
License: BSD 3-Clause License https://github.com/aaronsgiles/ymfm/blob/main/LICENSE
License: Public Domain
